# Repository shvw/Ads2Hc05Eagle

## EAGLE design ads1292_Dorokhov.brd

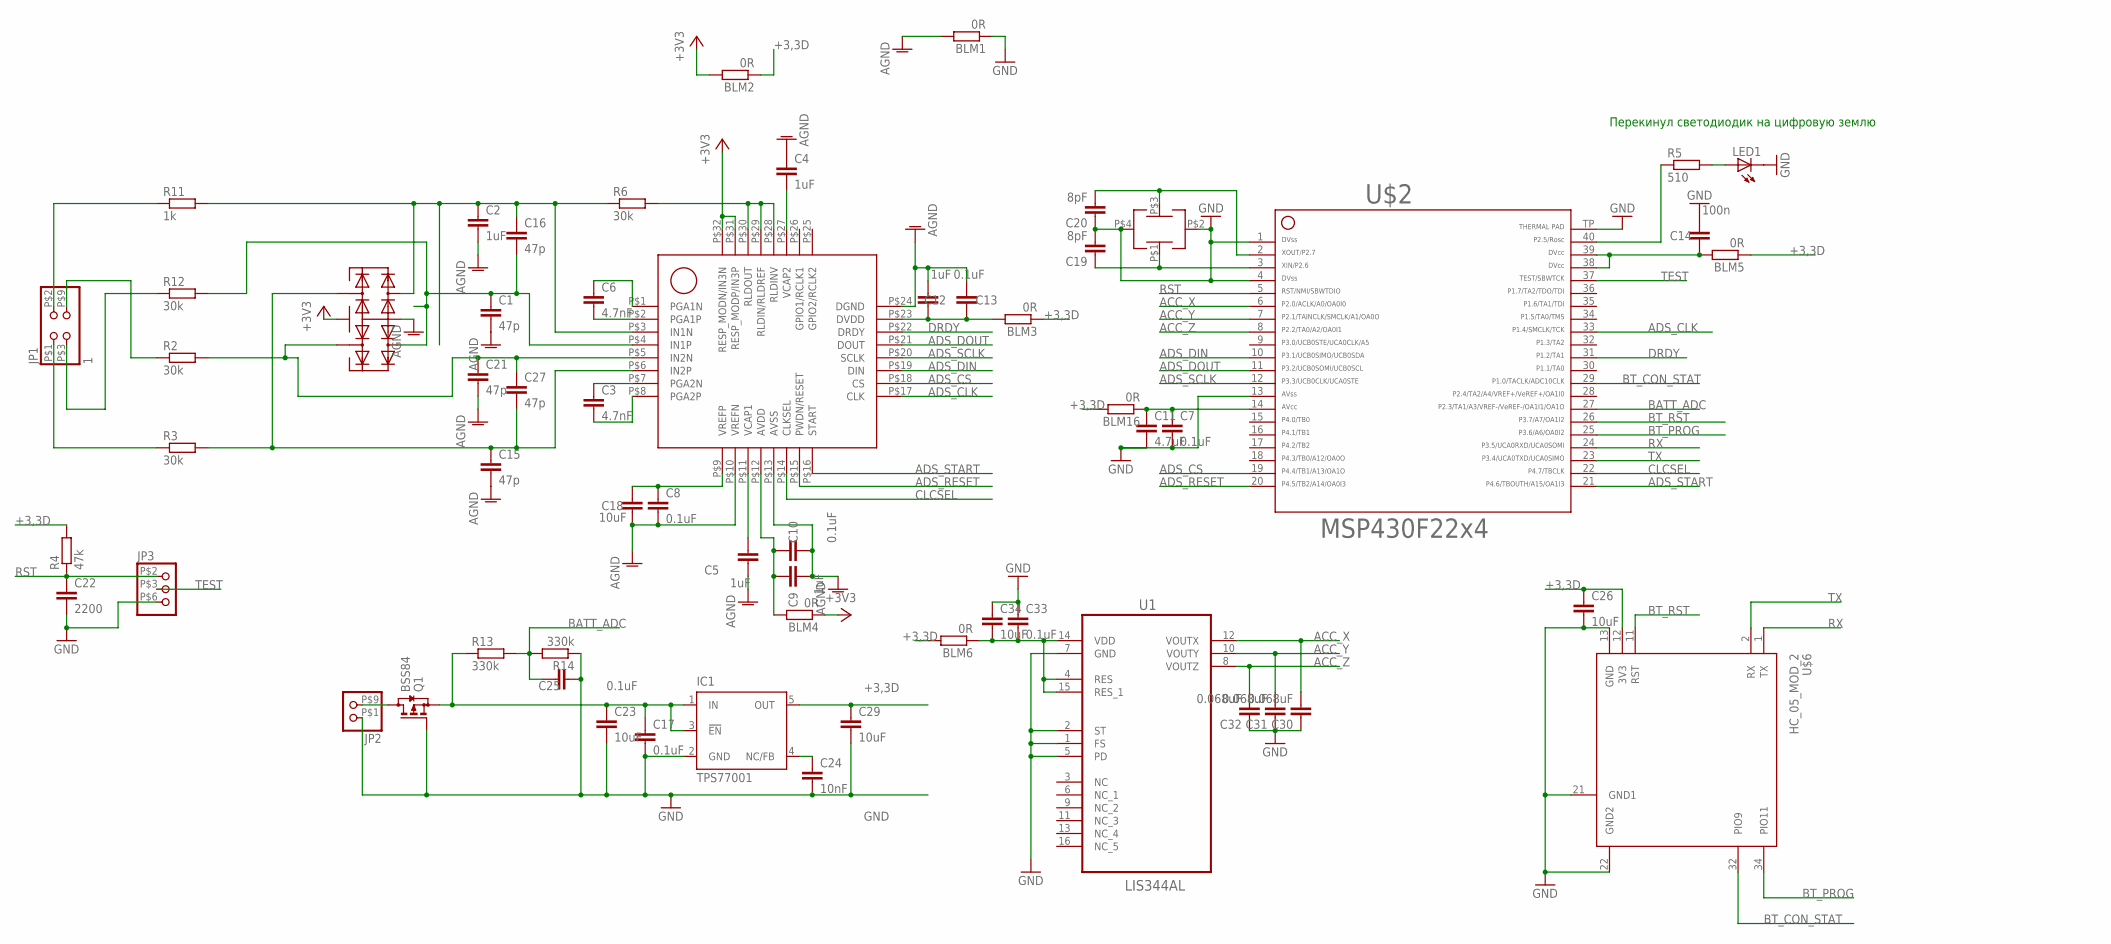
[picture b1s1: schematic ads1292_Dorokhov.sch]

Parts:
BLM1, BLM2, BLM3, BLM4, BLM5, BLM6, BLM16: 0R; SMD_0402
C1, C15, C16, C21, C27: 47p; SMD_0402
C2: 1uF; SMD_0603
C3, C6: 4.7nF; SMD_0402
C4, C5, C9, C12: 1uF; SMD_0402
C7, C8, C10, C13, C17, C25, C33: 0.1uF; SMD_0402
C11: 4.7uF; SMD_0603
C14: 100n; SMD_0402
C18, C23, C26, C29, C34: 10uF; SMD_0603
C19, C20: 8pF; SMD_0402
C22: 2200; SMD_0402
C24: 10nF; SMD_0402
C30, C31, C32: 0.068uF; SMD_0402
IC1: TPS77001; SOT23-DBV
JP1: 1; PINHEAD_SMD_2X2_2,5
JP2: PINHD-1X2SMD_2,5; PINHEAD_SMD_2X1_2,5
JP3: PINHD-1X3PROG_SMD; PROG_CONNECTOR_3PIN
LED1: LEDSML0603; SML0603
Q1: BSS84; SOT23
R2, R3, R12: 30k; R0603
R4: 47k; SMD_0402
R5: 510; SMD_0402
R6: 30k; SMD_0402
R11: 1k; R0603
R13, R14: 330k; SMD_0402
U1: LIS344AL; LGA16R65P4X4_400X400X160
U$1: ADS1292TQFP-32; TQFP-32
U$2: F22X4---RHA40; RHA40
U$3: ECS_16_CRYSTAL
U$4: DALC208; SOT23-6
U$6: HC_05_MOD_2; BLUETOOTH_SMD_MOD2

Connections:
+3,3D: BLM2.P$3 (1), BLM3.P$3 (1), BLM5.P$3 (1), BLM6.P$4 (2), BLM16.P$4 (2), C26.P$1 (1), C29.P$1 (1), IC1.5 (OUT), R4.P$4 (2), U$6.12 (3V3)
+3V3: BLM2.P$4 (2), BLM4.P$3 (1), U$1.P$31 (RESP_MODP/IN3P), U$1.P$32 (RESP_MODN/IN3N), U$4.2
ACC_X: C30.P$4 (2), U1.12 (VOUTX), U$2.6
ACC_Y: C31.P$4 (2), U1.10 (VOUTY), U$2.7
ACC_Z: C32.P$4 (2), U1.8 (VOUTZ), U$2.8
ADS_CLK: U$1.P$17 (CLK), U$2.33
ADS_CS: U$1.P$18 (CS), U$2.19
ADS_DIN: U$1.P$19 (DIN), U$2.10
ADS_DOUT: U$1.P$21 (DOUT), U$2.11
ADS_RESET: U$1.P$15 (PWDN/RESET), U$2.20
ADS_SCLK: U$1.P$20 (SCLK), U$2.12
ADS_START: U$1.P$16 (START), U$2.21
AGND: BLM1.P$4 (2), C1.P$4 (2), C2.P$2 (2), C4.P$3 (1), C5.P$4 (2), C8.P$4 (2), C9.P$4 (2), C10.P$4 (2), C12.P$4 (2), C13.P$4 (2), C15.P$4 (2), C18.P$2 (2), C21.P$4 (2), U$1.P$10 (VREFN), U$1.P$13 (AVSS), U$1.P$24 (DGND), U$4.5
BATT_ADC: C25.P$3 (1), R13.P$4 (2), R14.P$4 (2), U$2.27
BT_CON_STAT: U$2.29, U$6.32 (PIO9)
BT_PROG: U$2.25, U$6.34 (PIO11)
BT_RST: U$2.26, U$6.11 (RST)
CLCSEL: U$1.P$14 (CLKSEL), U$2.22
DRDY: U$1.P$22 (DRDY), U$2.31
GND: BLM1.P$3 (1), C7.P$4 (2), C11.P$2 (2), C14.P$4 (2), C17.P$4 (2), C19.P$4 (2), C20.P$3 (1), C22.P$4 (2), C23.P$2 (2), C24.P$4 (2), C25.P$4 (2), C26.P$2 (2), C29.P$2 (2), C30.P$3 (1), C31.P$3 (1), C32.P$3 (1), C33.P$3 (1), C34.P$1 (1), IC1.2 (GND), JP2.P$1 (1), JP3.P$6 (3), LED1.C, Q1.1 (G), R14.P$3 (1), U1.1 (FS), U1.2 (ST), U1.5 (PD), U1.7 (GND), U$2.1, U$2.4, U$2.13, U$2.TP, U$3.P$2, U$3.P$4, U$6.13 (GND), U$6.21 (GND1), U$6.22 (GND2)
unnamed: BLM3.P$4 (2), C12.P$3 (1), C13.P$3 (1), U$1.P$23 (DVDD)
unnamed: BLM16.P$3 (1), C7.P$3 (1), C11.P$1 (1), U$2.14
unnamed: BLM4.P$4 (2), C9.P$3 (1), C10.P$3 (1), U$1.P$12 (AVDD)
unnamed: C21.P$3 (1), C27.P$3 (1), R2.2, U$1.P$5 (IN2N), U$4.3
unnamed: C3.P$3 (1), U$1.P$7 (PGA2N)
unnamed: C3.P$4 (2), U$1.P$8 (PGA2P)
unnamed: C5.P$3 (1), U$1.P$11 (VCAP1)
unnamed: C4.P$4 (2), U$1.P$27 (VCAP2)
unnamed: C6.P$4 (2), U$1.P$2 (PGA1P)
unnamed: C6.P$3 (1), U$1.P$1 (PGA1N)
unnamed: C8.P$3 (1), C18.P$1 (1), U$1.P$9 (VREFP)
unnamed: BLM5.P$4 (2), C14.P$3 (1), U$2.38, U$2.39
unnamed: R5.P$3 (1), U$2.40
unnamed: C15.P$3 (1), C27.P$4 (2), R3.2, U$1.P$6 (IN2P), U$4.1
unnamed: C1.P$3 (1), C16.P$4 (2), R12.2, U$1.P$4 (IN1P), U$4.6
unnamed: C19.P$3 (1), U$2.3, U$3.P$1
unnamed: BLM6.P$3 (1), C33.P$4 (2), C34.P$2 (2), U1.4 (RES), U1.14 (VDD), U1.15 (RES_1)
unnamed: LED1.A, R5.P$4 (2)
unnamed: JP1.P$1 (1), R3.1
unnamed: JP1.P$9 (4), R2.1
unnamed: JP1.P$3 (3), R12.1
unnamed: C2.P$1 (1), C16.P$3 (1), R6.P$3 (1), R11.2, U$1.P$3 (IN1N), U$4.4
unnamed: JP1.P$2 (2), R11.1
unnamed: C20.P$4 (2), U$2.2, U$3.P$3
unnamed: JP2.P$9 (2), Q1.3 (D)
unnamed: R6.P$4 (2), U$1.P$28 (RLDINV), U$1.P$29 (RLDIN/RLDREF), U$1.P$30 (RLDOUT)
unnamed: C24.P$3 (1), IC1.4 (NC/FB)
RST: C22.P$3 (1), JP3.P$2 (1), R4.P$3 (1), U$2.5
RX: U$2.24, U$6.1 (TX)
TEST: JP3.P$3 (2), U$2.37
TX: U$2.23, U$6.2 (RX)
VLOAD: C17.P$3 (1), C23.P$1 (1), IC1.1 (IN), IC1.3 (!EN), Q1.2 (S), R13.P$3 (1)

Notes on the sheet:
Перекинул светодиодик на цифровую землю

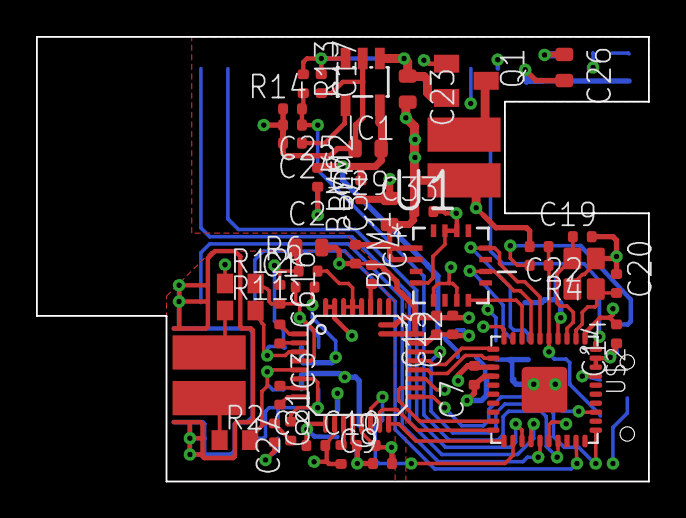
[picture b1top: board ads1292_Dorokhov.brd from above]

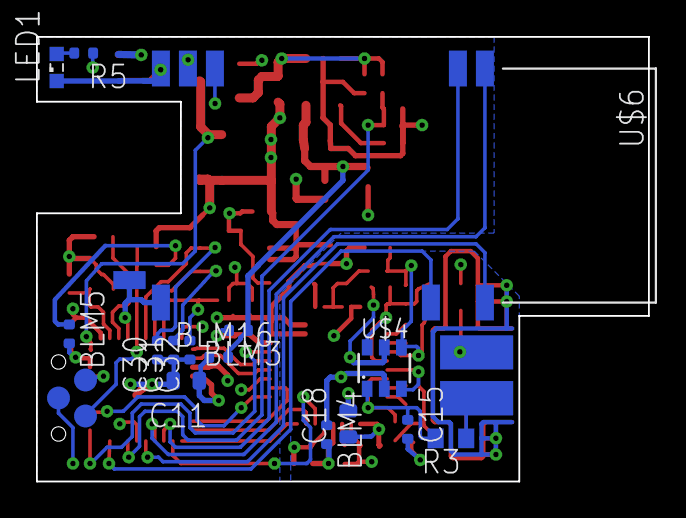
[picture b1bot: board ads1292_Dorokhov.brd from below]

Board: 4 copper layers, 34.0 x 24.7 mm, 61 parts (16 on the bottom side), 52 nets.

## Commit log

2014-11-13 Первая версия
2014-11-14 Rev.2.0
2014-11-14 REV_3.0
